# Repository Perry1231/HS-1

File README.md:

# HS-1

**HS-1 Kinematic Suit** is a full-body motion tracking system based on multiple ESP32-C3 nodes and BNO055 IMU sensors.

The project is designed to capture real-time body movement and orientation data, with support for sensor communication, data processing, and 3D visualization.

## Features

* Full-body motion tracking
* Multiple BNO055 IMU sensors
* ESP32-C3 sensor nodes
* I2C and UART communication
* Real-time motion data
* 3D model visualization
* Fusion 360 hardware design

## Technologies

* C++
* Python
* ESP32-C3
* BNO055
* I2C / UART
* PlatformIO
* Fusion 360

## Status

The project is currently under development.

### This README is awailable only for short term , until update

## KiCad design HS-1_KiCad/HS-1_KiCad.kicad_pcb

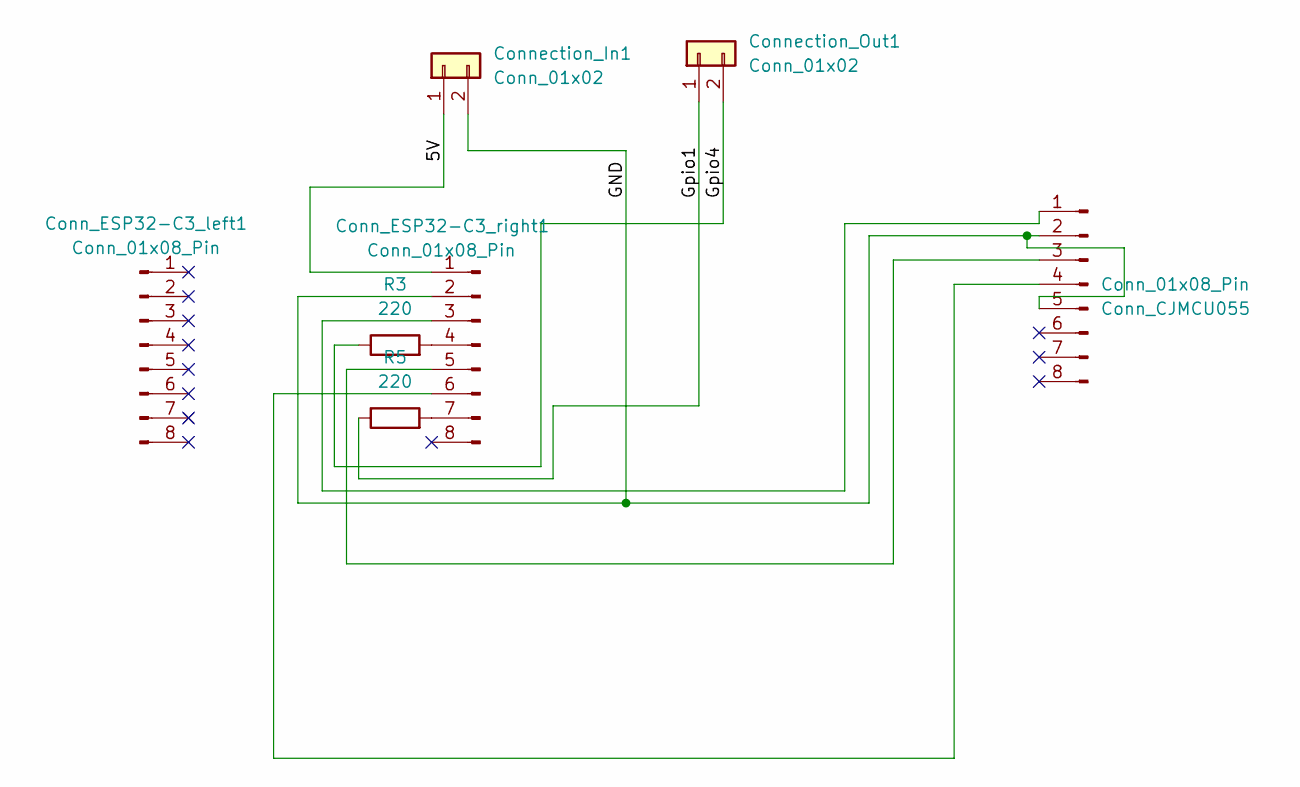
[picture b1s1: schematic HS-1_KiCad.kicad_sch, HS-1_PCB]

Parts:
Conn_CJMCU055: Conn_01x08_Pin; PinHeader_1x08_P2.54mm_Vertical
Conn_ESP32-C3_left1, Conn_ESP32-C3_right1: Conn_01x08_Pin; PinHeader_1x08_P2.54mm_Vertical
Connection_In1: Conn_01x02; JST_EH_S2B-EH_1x02_P2.50mm_Horizontal
Connection_Out1: Conn_01x02; JST_EH_S2B-EH_1x02_P2.50mm_Horizontal
R3, R5: 220; R_0805_2012Metric_Pad1.20x1.40mm_HandSolder

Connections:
/5V: Conn_ESP32-C3_right1.1, Connection_In1.1
/GND: Conn_CJMCU055.2, Conn_CJMCU055.5, Conn_ESP32-C3_right1.2, Connection_In1.2
/Gpio1: Connection_Out1.1, R5.1
/Gpio4: Connection_Out1.2, R3.1
unnamed: Conn_CJMCU055.1, Conn_ESP32-C3_right1.3
unnamed: Conn_CJMCU055.3, Conn_ESP32-C3_right1.5
unnamed: Conn_CJMCU055.4, Conn_ESP32-C3_right1.6
unnamed: Conn_ESP32-C3_right1.4, R3.2
unnamed: Conn_ESP32-C3_right1.7, R5.2

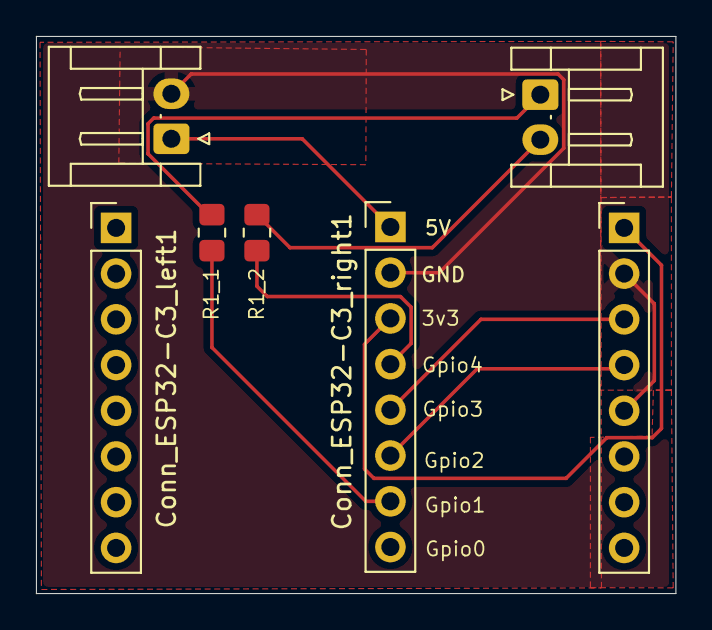
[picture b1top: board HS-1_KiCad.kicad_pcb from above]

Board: 2 copper layers, 35.5 x 30.9 mm, 7 parts (0 on the bottom side), 9 nets.
